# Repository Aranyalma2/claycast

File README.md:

**ClayCast** is a modular wireless control system for clay pigeon shooting ranges.  
It enables field centralized game management via a touchscreen **HMI device**, which controls up to 10 clay thrower machines through a wireless **Modbus RTU** network.  
Communication is handled by **controller node** that act as wireless relays to **client devices** attached to each clay thrower.

## 🎯 Features

- **Modular, multi-device architecture**: HMI (master), Controller (relay), and Client (thrower control)
- **Game management interface** via 7-inch touchscreen HMI
  - Enable/Disable machines (up to 10)
  - Pre-configure next game (max throw, double, triple)
  - Monitor clay disk levels with low-ammo alarms
  - Game screen
  - Summary screen
- **Wireless Modbus RTU bridging** over HC12 (~433MHz)
  - Up to **255 clients** per controller (practically limited to fewer)
  - Reliable full-frame encapsulation (no packet fragmentation)
- **Low-latency protocol** using UART and lightweight firmware
- Built with **Arduino framework**, **Atmega328p**, **ESP32**, and **HC12 modules**
- **Open and customizable** — easy to extend or adapt for other range configurations

## 🧩 Core Components

**ClayCast** consists of three main components:

### 💠 HMI Device
- Acts as the **Modbus RTU Master**
- Human-Machine Interface with touchscreen
- Controls up to **10 clay thrower machines**
- Manages and runs the **preconfigured game**
- Monitors **ammo levels** and triggers alarms if low
- Central command and monitoring unit for the entire system  
[More about here](hmi/README.md)

### 🔸 Controller
- Acts as a wireless Modbus RTU bridge
- Receives Modbus requests from a master device via UART (RS485)
- Encapsulates and broadcasts packets wirelessly to clients
- Receives wireless responses, decapsulates, and forwards them to the master  
[More about here](controller/README.md)

### 🔹 Client
- Identified by a unique Modbus slave address
- Controls an individual clay thrower machine
- Listens for Modbus requests, executes commands (e.g., fire), and returns status
- Response-only device; never initiates communication  
[More about here](client/README.md)

## 📡 Communication Flow

1. HMI sends Modbus RTU request to Controller via UART (RS485).
2. Controller encapsulates and transmits over HC12 radio.
3. Target Client receives, executes, and responds.
4. Controller decapsulates and returns response to HMI.

## 🛠️ Hardware Requirements

- **HMI Device**:
  - Kinco HMI [GL070E](https://en.kinco.cn/productdetail/gl070e90.html)

- **Controller**:
  - Arduino (Atmega328p)
  - HC12 radio module
  - RS485 interface to HMI (Modbus master)

- **Client**:
  - Arduino (Atmega328p)
  - HC12 radio module
  - Clay thrower trigger mechanism (relay, microswitch, etc.)

## 📦 Modbus Support

Clients implement:
- **Trigger register** – Fire the clay thrower
- **Status registers** – Report state, diagnostics, or ammo level

## 🚧 Status & Development Milestones

🛠️ Currently Under Development — Working Prototype Deployed in Test Field

- ✅ **Prototype Hardware Evaluation**  
  Initial testing and validation of temporary hardware components.

- ✅ **Firmware Architecture Design**  
  Core structure and logic for both controller and client firmware defined and implemented.

- ✅ **Interim Hardware Integration**  
  Temporary hardware assembled and tested for early firmware and communication debugging.

- ✅ **Wireless Communication Tester**  
  Radio signal testing module completed to assess transmission range and reliability.

- 🔧 **Final Hardware Assembly** *(In Progress)*  
  Development and deployment of production-ready, dedicated hardware.
  
- 🚀 **Human-Machine Interface (HMI)** *(In Testing)*  
  - Game customizability, fire control, data logging  
  - Ammo monitoring with alarms  
  - Controls up to 10 clay throwers

## 🔀 Alternative use

Create a Modbus RTU bridge over the air with 2 or more **Controllers**. However, radio medium usage is not controlled, so it is easy to cause interference. Incidentally it does not include any error detection and/or correction, leaving everything to the application layer protocol.
Not ready for any production usage.

---

## 📜 License

This project is licensed under the MIT License. See the [LICENSE](LICENSE.md) file for details.

---

## 🤝 Contributions

Made with ❤️ by <a href="https://github.com/Aranyalma2" target="_blank">Aranyalma2</a>

This is a self-maintained project. Feel free to use, fork, or modify it. Feedback and suggestions are always welcome!

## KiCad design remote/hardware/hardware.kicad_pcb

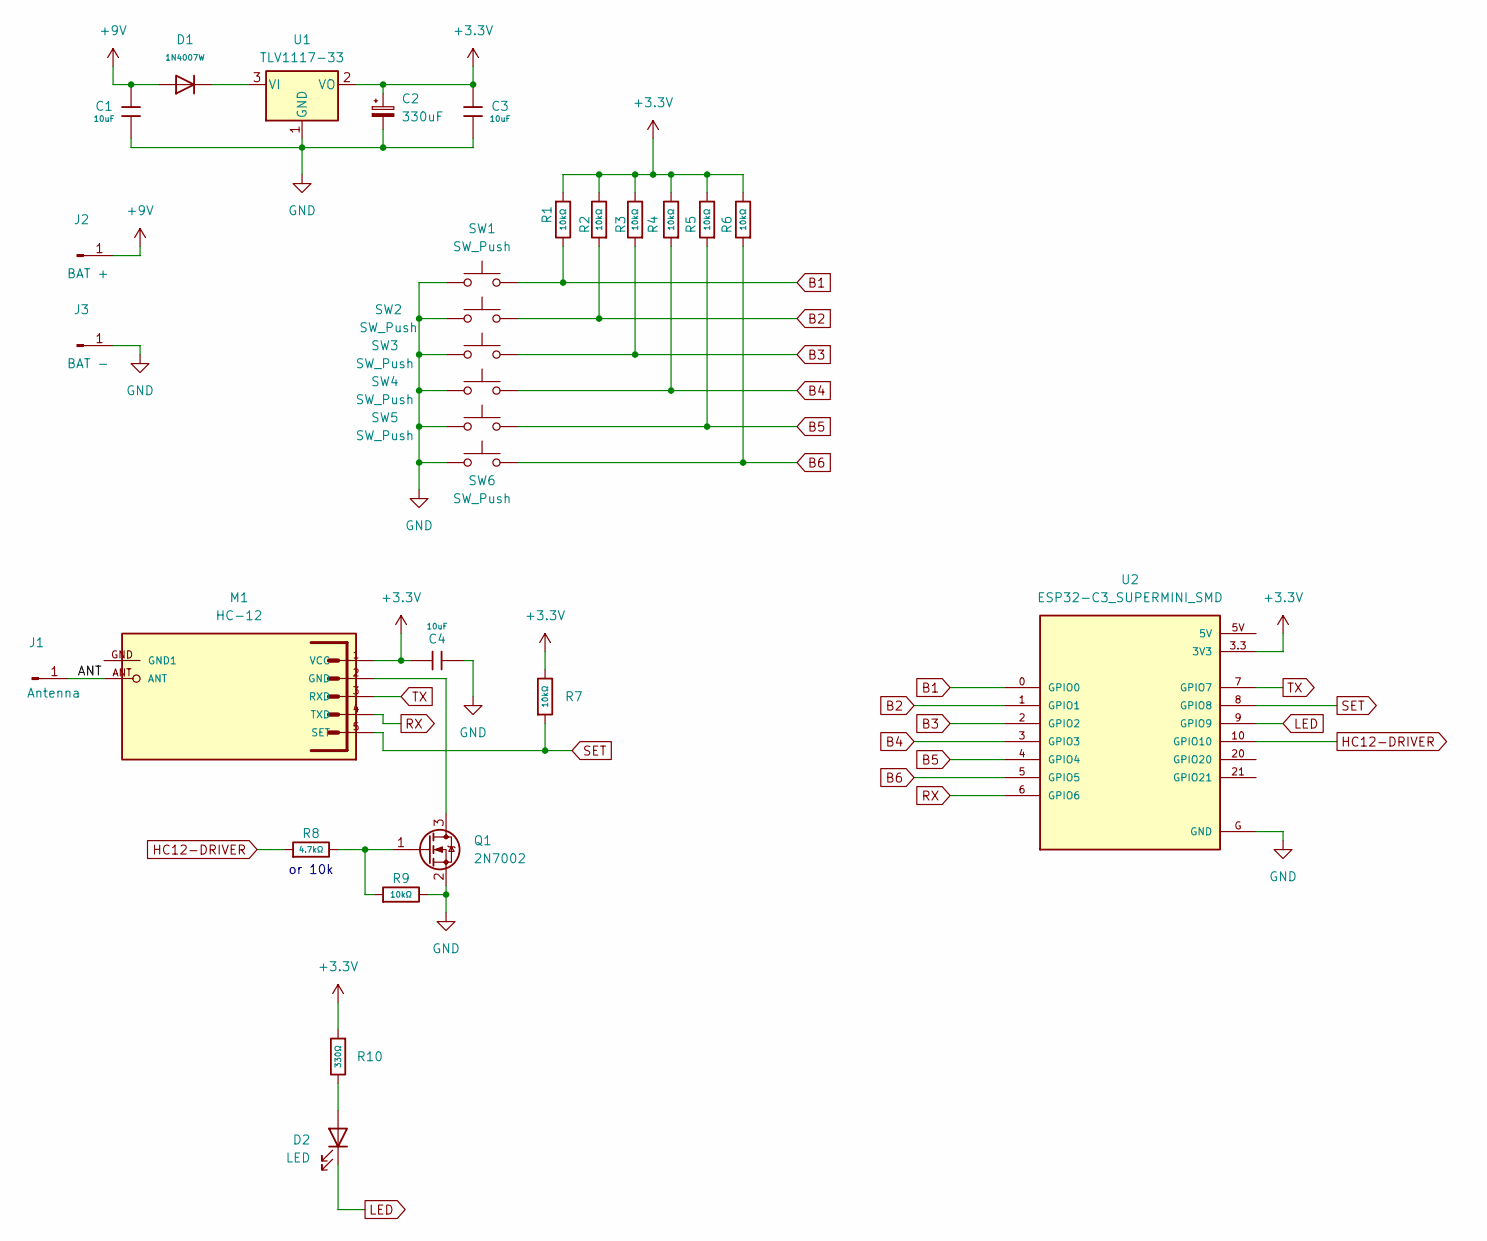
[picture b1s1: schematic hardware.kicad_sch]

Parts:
C1, C3, C4: 10uF; C_1206; Voltage Rated 6V; Tolerance ±10%; Part CL31A106KBHNNNE; LCSC C13585
C2: 330uF; CP_Radial_D6.3mm_P2.50mm
D1: 1N4007W; D_SMB; Part 1N4007W; LCSC C18199088
D2: LED; LED_1206_3216Metric_Pad1.42x1.75mm_HandSolder
J1: Antenna; PinHeader_1x01_P1.00mm_Vertical
J2: BAT +; PinHeader_1x01_P1.00mm_Vertical
J3: BAT -; PinHeader_1x01_P1.00mm_Vertical
M1: HC-12; MA05-1
Q1: 2N7002; SOT-23
R1, R2, R3, R4, R5, R6, R7, R9: 10kΩ; R_0805; Overload Voltage (Max) 200V; Tolerance ±1%; Part 1206W4F1002T5E; LCSC C17902
R8: 4.7kΩ; R_0805; Overload Voltage (Max) 200V; Tolerance ±1%; Part 1206W4F1002T5E; LCSC C17902
R10: 330Ω; R_1206
SW1, SW2, SW3, SW4, SW5, SW6: SW_Push; SW_Push_1P1T_NO_E-Switch_TL3301NxxxxxG
U1: TLV1117-33; TO-252-2
U2: ESP32-C3_SUPERMINI_SMD; MODULE_ESP32-C3_SUPERMINI

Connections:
+3.3V: C2.1, C3.1, C4.1, M1.1 (VCC), R1.1, R2.2, R3.2, R4.2, R5.2, R6.2, R7.2, R10.1, U1.2 (VO), U2.3.3 (3V3)
+9V: C1.1, D1.2, J2.1
/ANT: J1.1, M1.ANT
B1: R1.2, SW1.1, U2.0 (GPIO0)
B2: R2.1, SW2.1, U2.1 (GPIO1)
B3: R3.1, SW3.1, U2.2 (GPIO2)
B4: R4.1, SW4.1, U2.3 (GPIO3)
B5: R5.1, SW5.1, U2.4 (GPIO4)
B6: R6.1, SW6.1, U2.5 (GPIO5)
GND: C1.2, C2.2, C3.2, C4.2, J3.1, Q1.2 (S), R9.2, SW1.2, SW2.2, SW3.2, SW4.2, SW5.2, SW6.2, U1.1 (GND), U2.G (GND)
HC12-DRIVER: R8.1, U2.10 (GPIO10)
LED: D2.1 (K), U2.9 (GPIO9)
unnamed: D2.2 (A), R10.2
unnamed: M1.2 (GND), Q1.3 (D)
unnamed: Q1.1 (G), R8.2, R9.1
unnamed: D1.1, U1.3 (VI)
RX: M1.4 (TXD), U2.6 (GPIO6)
SET: M1.5 (SET), R7.1, U2.8 (GPIO8)
TX: M1.3 (RXD), U2.7 (GPIO7)

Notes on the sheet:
or 10k

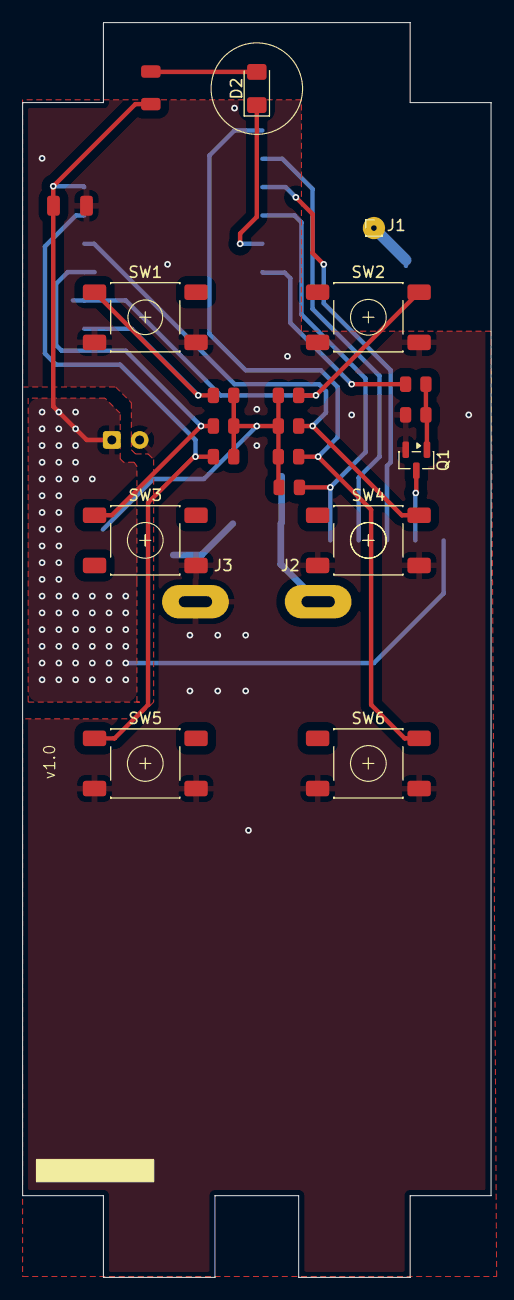
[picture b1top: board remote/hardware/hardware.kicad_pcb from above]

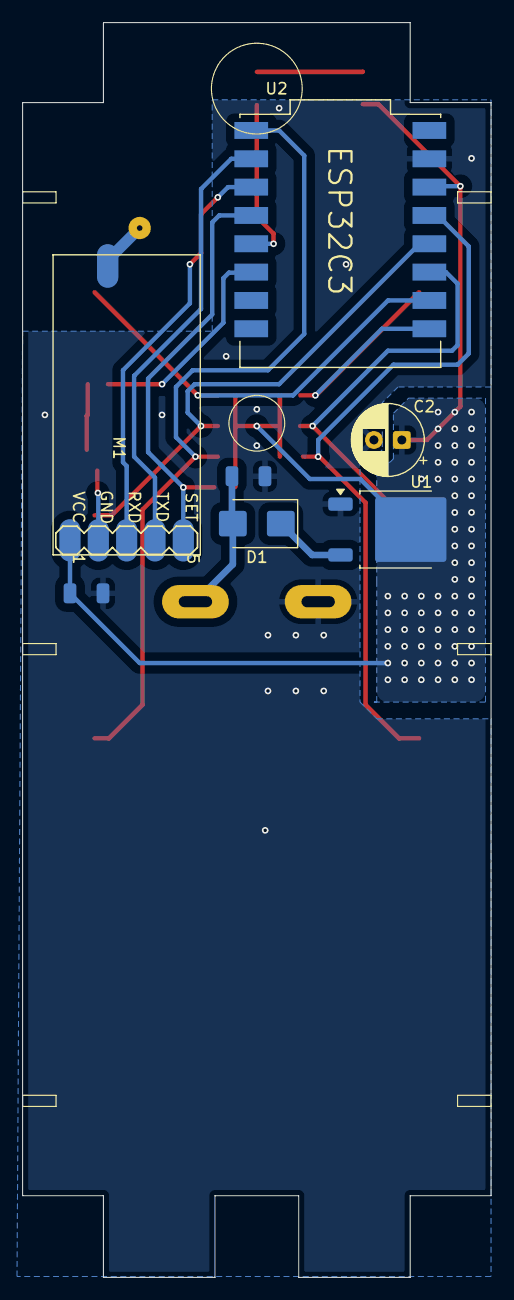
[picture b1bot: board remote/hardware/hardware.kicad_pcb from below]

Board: 2 copper layers, 42.0 x 112.5 mm, 29 parts (7 on the bottom side), 19 nets.

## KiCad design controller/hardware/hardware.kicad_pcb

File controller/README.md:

## The core tasks of the controller

### 📡 Serial Communication Setup

- Uses **hardware `Serial`** for UART communication with the Modbus RTU master
- Uses **`SoftwareSerial`** or a secondary UART for the HC12 module

### 📦 Modbus RTU Data Encapsulation

- Reads Modbus RTU requests from UART
- Wraps requests in a custom protocol header for wireless transmission via HC12

### 🚀 HC12 Transmission

- Sends encapsulated Modbus RTU requests over HC12
- Receives wrapped responses wirelessly from the client

### 📥 Response Processing

- Validates incoming wrapped responses
- Unwraps the Modbus RTU data
- Forwards it back to the Modbus master via hardware `Serial`

### 🧪 Test Mode (Enabled via A0)

If **pin A0 is HIGH** during power-up or reset, the controller enters **testing mode**:

- It disables Modbus forwarding
- Instead, it periodically sends test messages over HC12 in the following format:

`Testing in progress: {n}`

- These messages are wrapped in the standard packet format below and sent every ~500ms
- `n` is an incrementing counter used to test communication reliability and packet loss

This mode is useful for verifying wireless reception, packet framing, and performance of the client-side system.

---

## 📦 Data Encapsulation Format

All HC12-transmitted messages use a consistent wrapper protocol:

```
+--------------------+---------+----------------------+
| Field              | Size    | Description          |
+--------------------+---------+----------------------+
| Start byte (0xAA)  | 1 Byte  | Packet start byte    |
| Data size          | 2 Bytes | Data size            |
| Data               | X Bytes | Modbus RTU package   |
| Checksum           | 2 Bytes | Size + Data checksum |
| End byte (0x55)    | 1 Byte  | Packet end byte      |
+--------------------+---------+----------------------+
```

- The `Data` section contains a complete Modbus RTU request or response
- Destination is determined by the Modbus RTU address field inside the data

## 🔧 Notes

- Make sure the HC12 modules are on the same channel (e.g. `CH050`)
- The serial and HC12 baudrates may differ, but it is recommended to choose equal and low rates. However, it is important to match the timing of the packet frames.

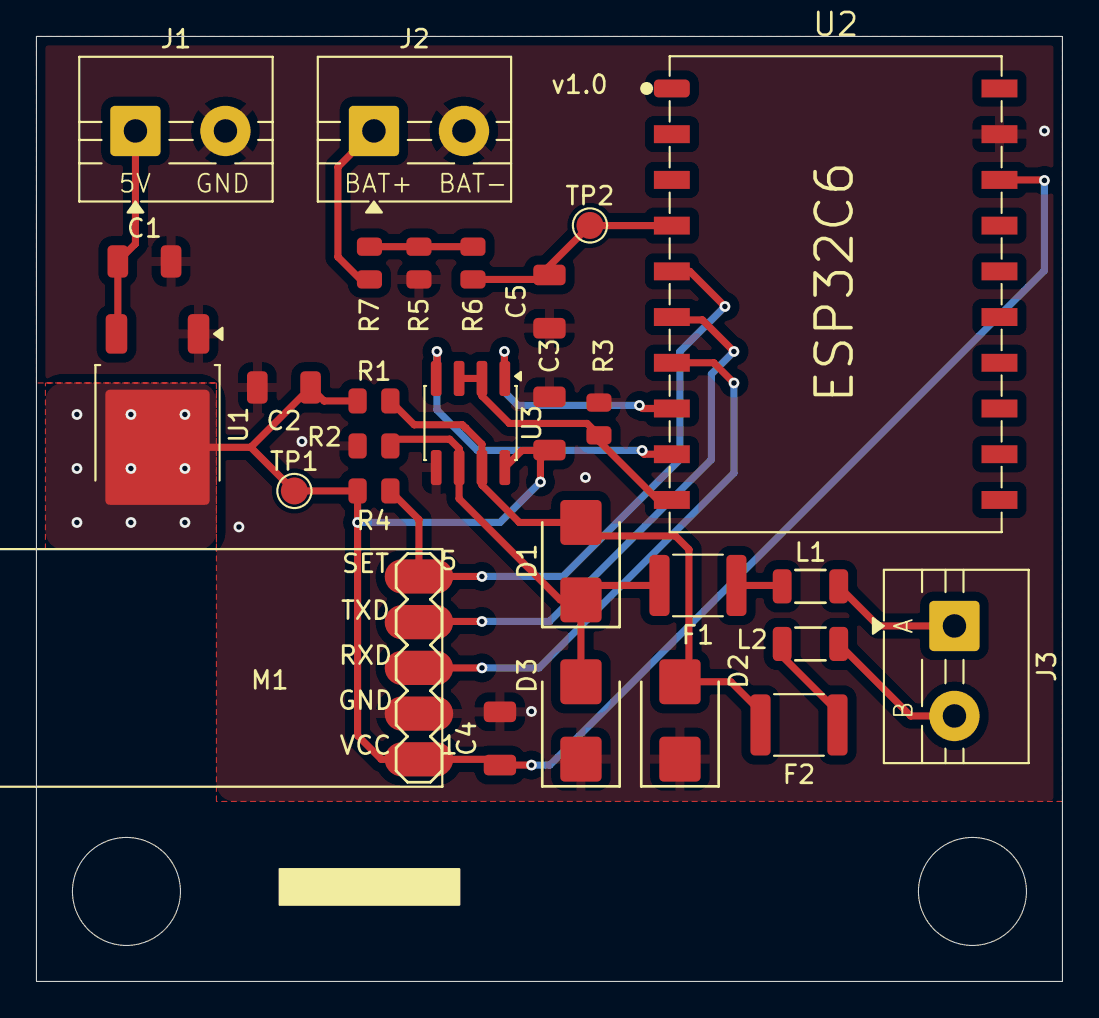
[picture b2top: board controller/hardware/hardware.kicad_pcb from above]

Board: 2 copper layers, 57.0 x 52.5 mm, 28 parts (0 on the bottom side), 18 nets.

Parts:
C1, C2, C4: 10uF; C_1206
C3, C5: 100nF; C_1206
D1, D2, D3: SMBJ12CA; D_SMB
F1, F2: BSMD1812-100-30V
J1, J2, J3: Screw_Terminal_01x02; TerminalBlock_MaiXu_MX126-5.0-02P_1x02_P5.00mm
L1, L2: 10uH; L_1206
M1: HC-12; MA05-1
R1, R2, R3, R4: 10kΩ; R_0805
R5: 1MΩ; R_0805
R6: 1kΩ; R_0805
R7: 100kΩ; R_0805
TP1: 3V3; TestPoint_Pad_D1.5mm
TP2: BAT_V; TestPoint_Pad_D1.5mm
U1: TLV1117-33; TO-252-2
U2: ESP32-C6-SuperMini; ESP32-C6-SuperMini_SMD
U3: MAX3485; SOIC-8_3.9x4.9mm_P1.27mm

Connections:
+3.3V: C2.1, C3.1, C4.1, M1.1 (VCC), R1.1, R4.2, TP1.1, U1.2 (VO), U2.13 (3V3), U3.8 (VCC)
+5V: C1.1, J1.1, U1.3 (VI)
+BATT: J2.1, R5.2
BAT_MEASURE: C5.2, R6.1, TP2.1, U2.4 (GPIO1)
GND: C1.2, C2.2, C3.2, C4.2, C5.1, D2.1, D3.1, J1.2, J2.2, M1.2 (GND), R2.2, R3.2, R7.1, U1.1 (GND), U2.12 (GND), U3.5 (GND)
unnamed: F1.2, L1.1
unnamed: F2.2, L2.1
unnamed: R5.1, R6.2, R7.2
unnamed: D1.1, D3.2, F1.1, R2.1, U3.6 (A)
unnamed: D1.2, D2.2, F2.1, R1.2, U3.7 (B)
RS485-1_A: J3.1, L1.2
RS485-1_B: J3.2, L2.2
RX: M1.4 (TXD), U2.6 (GPIO3)
RX1: U2.8 (GPIO5), U3.1 (RO)
SET: M1.5 (SET), R4.1, U2.5 (GPIO2)
TX: M1.3 (RXD), U2.7 (GPIO4)
TX1: U2.9 (GPIO6), U3.4 (DI)
TX1_EN: R3.1, U2.10 (GPIO7), U3.2 (~RE), U3.3 (DE)

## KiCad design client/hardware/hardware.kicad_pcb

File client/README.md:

## The Core Tasks of the Client

### 📡 Setup Serial Communication

- Uses `SoftwareSerial` for UART communication with the HC12 wireless module  
- Uses hardware `Serial` for debug output

### 📥 Process Modbus RTU Requests

- Waits for incoming encapsulated Modbus RTU requests over HC12  
- Unwraps received packets and validates structure and checksum

### ⚙️ Handle Modbus Logic

- Supports:
  - Read Holding Registers (`0x03`)
  - Write Single Register (`0x06`)
- Maintains internal holding registers for:
  - Device ID
  - Shoot trigger
  - Success flag (Complex/Simple)
- Triggers actions based on incoming Modbus commands

#### 🧮 Registers

**Holding Register (4xxxxx)**
```
+---------+----------------------------+
| Address | Description                |
+---------+----------------------------+
| 0x00    | Modbus Address (Read only) |
| 0x01    | Fire (automatic zeroing)   |
| 0x02    | IN1 (zeroing at fire)      |
| 0x03    | IN2 (Raw)                  |
+---------+----------------------------+
```

### 📤 Transmit Modbus RTU Responses

- Wraps Modbus RTU responses with a protocol header  
- Sends the encapsulated data back via HC12

---

## 📦 Data Encapsulation Format

All HC12-transmitted messages use a consistent wrapper protocol:

```
+--------------------+---------+----------------------+
| Field              | Size    | Description          |
+--------------------+---------+----------------------+
| Start byte (0xAA)  | 1 Byte  | Packet start byte    |
| Data size          | 2 Bytes | Data size            |
| Data               | X Bytes | Modbus RTU package   |
| Checksum           | 2 Bytes | Size + Data checksum |
| End byte (0x55)    | 1 Byte  | Packet end byte      |
+--------------------+---------+----------------------+
```

- The `Data` section contains a complete Modbus RTU request or response
- Destination is determined by the Modbus RTU address field inside the data

---

## 🔧 Notes

- Make sure the HC12 modules are on the same channel (e.g. `CH050`)  
- The client listens for shoot commands and activates GPIO pins accordingly

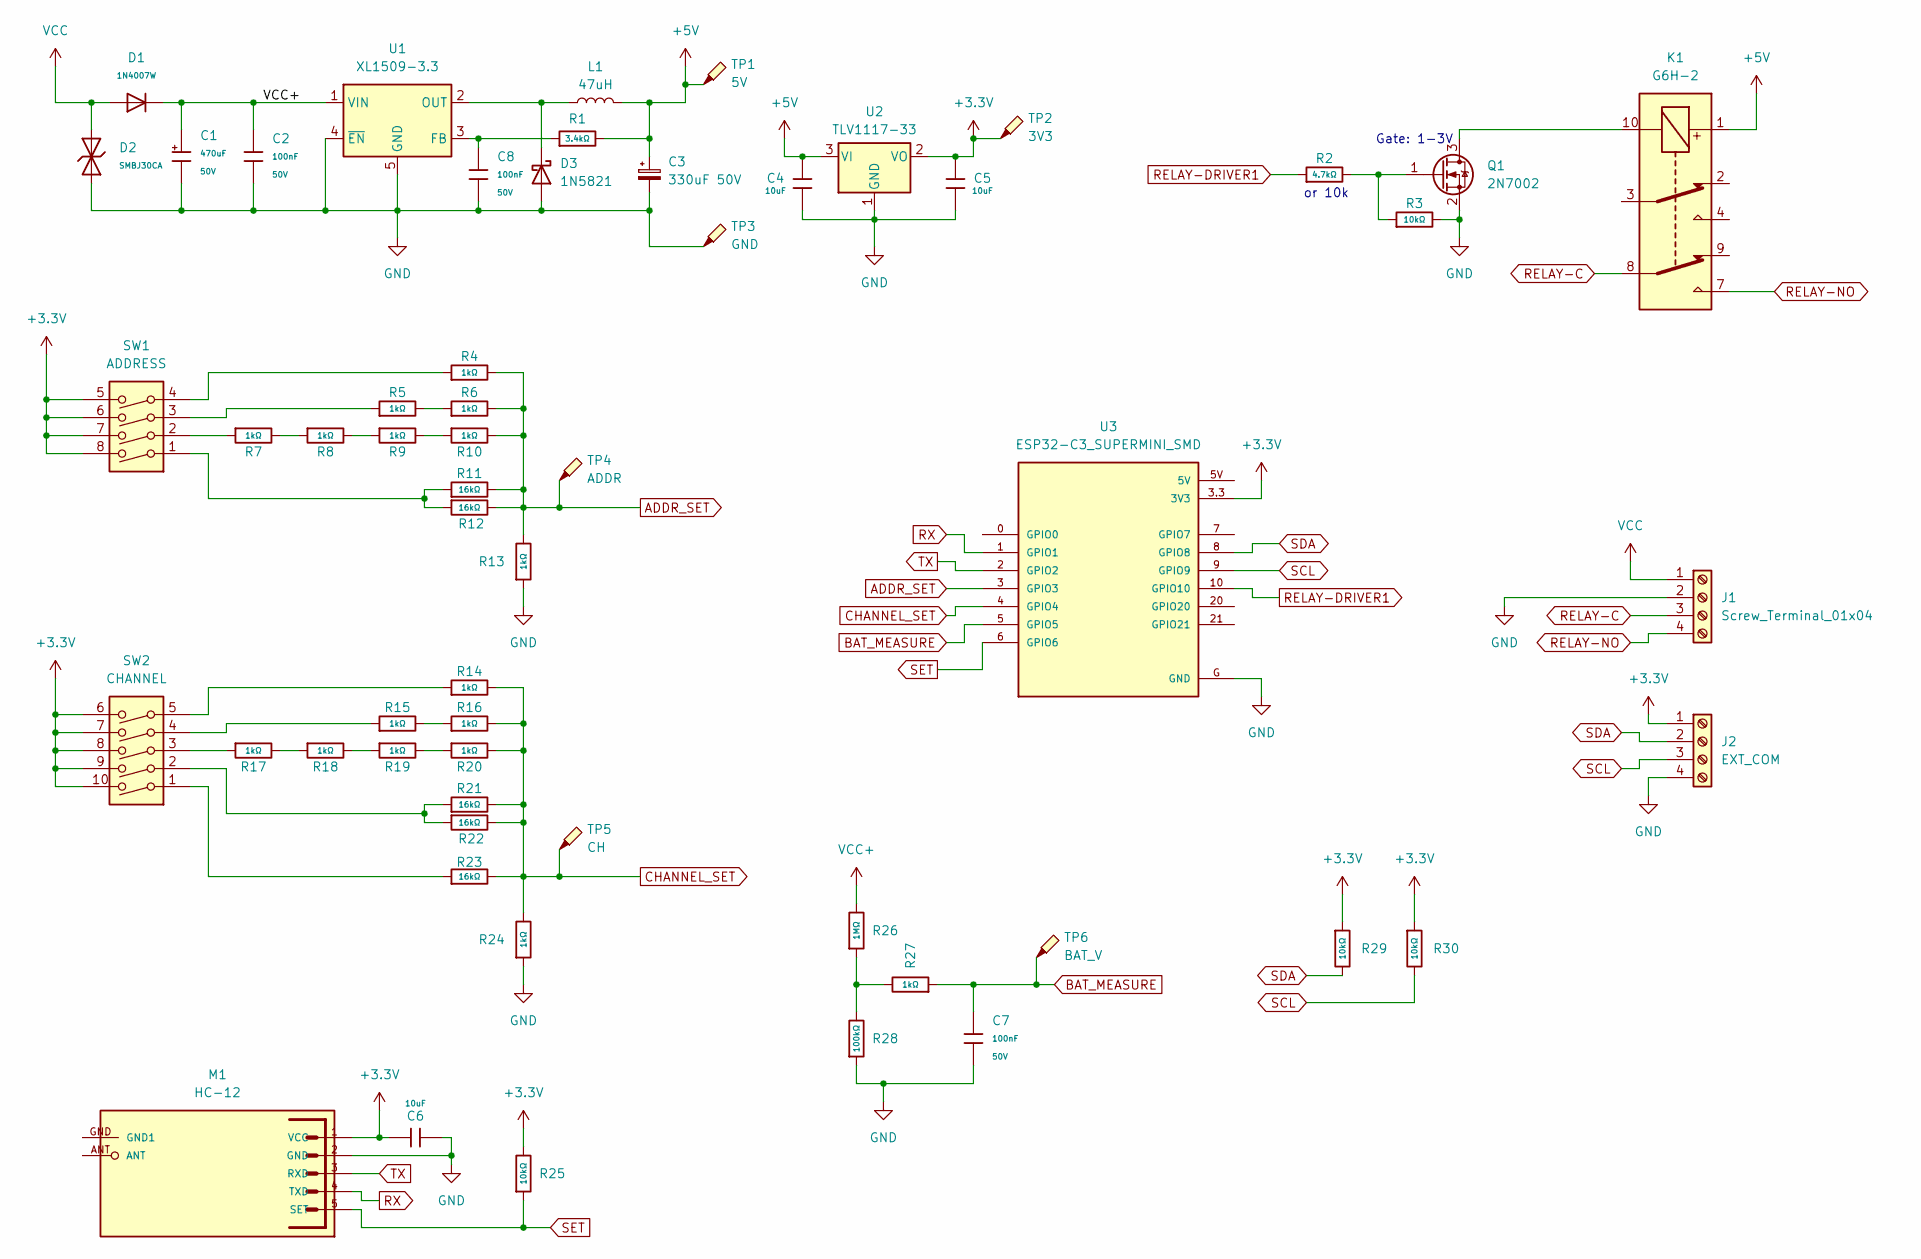
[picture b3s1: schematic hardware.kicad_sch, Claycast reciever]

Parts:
C1: 470uF; C_Plugin,D10xL16mm; Voltage Rated 50V; Part EGT477M1HG16RRS0P; LCSC C3015599
C2, C7, C8: 100nF; C_1206; Voltage Rated 50V; Tolerance ±10%; Part CL31B104KBCNNNC; LCSC C24497
C3: 330uF 50V; CP_Radial_D6.3mm_P2.50mm
C4, C5, C6: 10uF; C_1206; Voltage Rated 6V; Tolerance ±10%; Part CL31A106KBHNNNE; LCSC C13585
D1: 1N4007W; D_SMB; Part 1N4007W; LCSC C18199088
D2: SMBJ30CA; D_SMB; Breakdown Voltage 33.3V; Part SMBJ30CA; LCSC C2925441
D3: 1N5821; D_SMB
J1: Screw_Terminal_01x04; General Connector 4P 3.5mm - Socket
J2: EXT_COM; JST_PH_B4B-PH-K_1x04_P2.00mm_Vertical
K1: G6H-2; Relay_DPDT_Omron_G6H-2
L1: 47uH; L_Radial_D7.0mm_P3.00mm
M1: HC-12; MA05-1
Q1: 2N7002; SOT-23
R1: 3.4kΩ; R_0805; Overload Voltage (Max) 150V; Tolerance ±1%; Part 0805W8F3303T5E; LCSC C17629
R2: 4.7kΩ; R_0805; Overload Voltage (Max) 200V; Tolerance ±1%; Part 1206W4F1002T5E; LCSC C17902
R3, R25, R29, R30: 10kΩ; R_0805; Overload Voltage (Max) 200V; Tolerance ±1%; Part 1206W4F1002T5E; LCSC C17902
R4, R5, R6, R7, R8, R9, R10, R13, R14, R15, R16, R17, R18, R19, R20, R24, R27: 1kΩ; R_0805; Overload Voltage (Max) 200V; Tolerance ±1%; Part 1206W4F1002T5E; LCSC C17902
R11, R12, R21, R22, R23: 16kΩ; R_0805; Overload Voltage (Max) 200V; Tolerance ±1%; Part 1206W4F1002T5E; LCSC C17902
R26: 1MΩ; R_0805; Overload Voltage (Max) 200V; Tolerance ±1%; Part 1206W4F1002T5E; LCSC C17902
R28: 100kΩ; R_0805; Overload Voltage (Max) 200V; Tolerance ±1%; Part 1206W4F1002T5E; LCSC C17902
SW1: ADDRESS; SW_DIP_SPSTx04_Slide_9.78x12.34mm_W7.62mm_P2.54mm
SW2: CHANNEL; SW_DIP_SPSTx05_Slide_9.78x14.88mm_W7.62mm_P2.54mm
TP1: 5V; TestPoint_Pad_D1.5mm
TP2: 3V3; TestPoint_Pad_D1.5mm
TP3: GND; TestPoint_Pad_D1.5mm
TP4: ADDR; TestPoint_Pad_D1.5mm
TP5: CH; TestPoint_Pad_D1.5mm
TP6: BAT_V; TestPoint_Pad_D1.5mm
U1: XL1509-3.3; SOIC-8_3.9x4.9mm_P1.27mm
U2: TLV1117-33; TO-252-2
U3: ESP32-C3_SUPERMINI_SMD; MODULE_ESP32-C3_SUPERMINI

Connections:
+3.3V: C5.1, C6.1, J2.1, M1.1 (VCC), R25.2, R29.1, R30.1, SW1.5, SW1.6, SW1.7, SW1.8, SW2.6, SW2.7, SW2.8, SW2.9, SW2.10, TP2.1, U2.2 (VO), U3.3.3 (3V3)
+5V: C3.1, C4.1, K1.1, L1.2, R1.2, TP1.1, U2.3 (VI)
ADDR_SET: R4.2, R6.2, R10.2, R11.2, R12.2, R13.2, TP4.1, U3.3 (GPIO3)
BAT_MEASURE: C7.2, R27.1, TP6.1, U3.5 (GPIO5)
CHANNEL_SET: R14.2, R16.2, R20.2, R21.2, R22.2, R23.2, R24.2, TP5.1, U3.4 (GPIO4)
GND: C1.2, C2.2, C3.2, C4.2, C5.2, C6.2, C7.1, C8.2, D2.1, D3.2 (A), J1.2, J2.4, M1.2 (GND), Q1.2 (S), R3.2, R13.1, R24.1, R28.1, TP3.1, U1.4 (~EN), U1.5 (GND), U1.6 (GND), U1.7 (GND), U1.8 (GND), U2.1 (GND), U3.G (GND)
unnamed: D3.1 (K), L1.1, U1.2 (OUT)
unnamed: K1.10, Q1.3 (D)
unnamed: Q1.1 (G), R2.2, R3.1
unnamed: R4.1, SW1.4
unnamed: R5.1, SW1.3
unnamed: R5.2, R6.1
unnamed: R7.1, SW1.2
unnamed: R7.2, R8.1
unnamed: R8.2, R9.1
unnamed: R9.2, R10.1
unnamed: R11.1, R12.1, SW1.1
unnamed: R14.1, SW2.5
unnamed: R15.1, SW2.4
unnamed: R15.2, R16.1
unnamed: R17.1, SW2.3
unnamed: R17.2, R18.1
unnamed: R18.2, R19.1
unnamed: R19.2, R20.1
unnamed: R21.1, R22.1, SW2.2
unnamed: R23.1, SW2.1
unnamed: R26.1, R27.2, R28.2
unnamed: C8.1, R1.1, U1.3 (FB)
RELAY-C: J1.3, K1.8
RELAY-DRIVER1: R2.1, U3.10 (GPIO10)
RELAY-NO: J1.4, K1.7
RX: M1.4 (TXD), U3.1 (GPIO1)
SCL: J2.3, R30.2, U3.9 (GPIO9)
SDA: J2.2, R29.2, U3.8 (GPIO8)
SET: M1.5 (SET), R25.1, U3.6 (GPIO6)
TX: M1.3 (RXD), U3.2 (GPIO2)
VCC: D1.2, D2.2, J1.1
VCC+: C1.1, C2.1, D1.1, R26.2, U1.1 (VIN)

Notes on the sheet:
or 10k
Gate: 1-3V

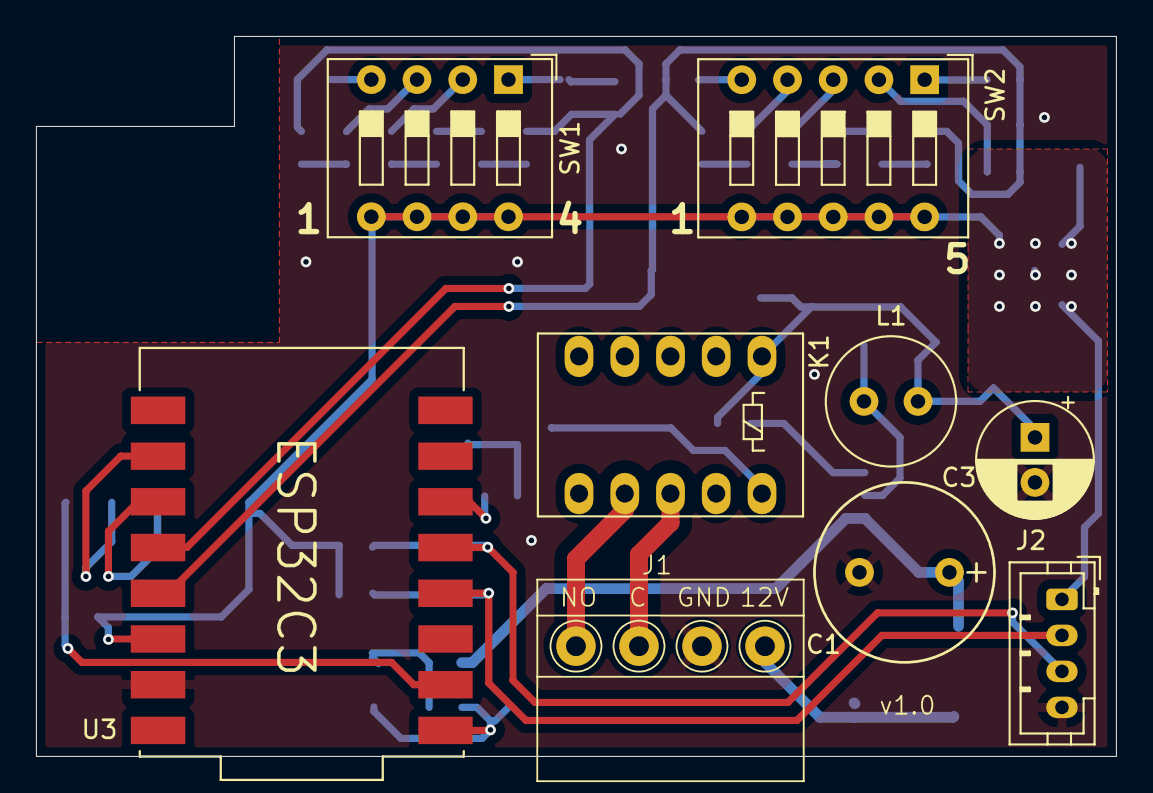
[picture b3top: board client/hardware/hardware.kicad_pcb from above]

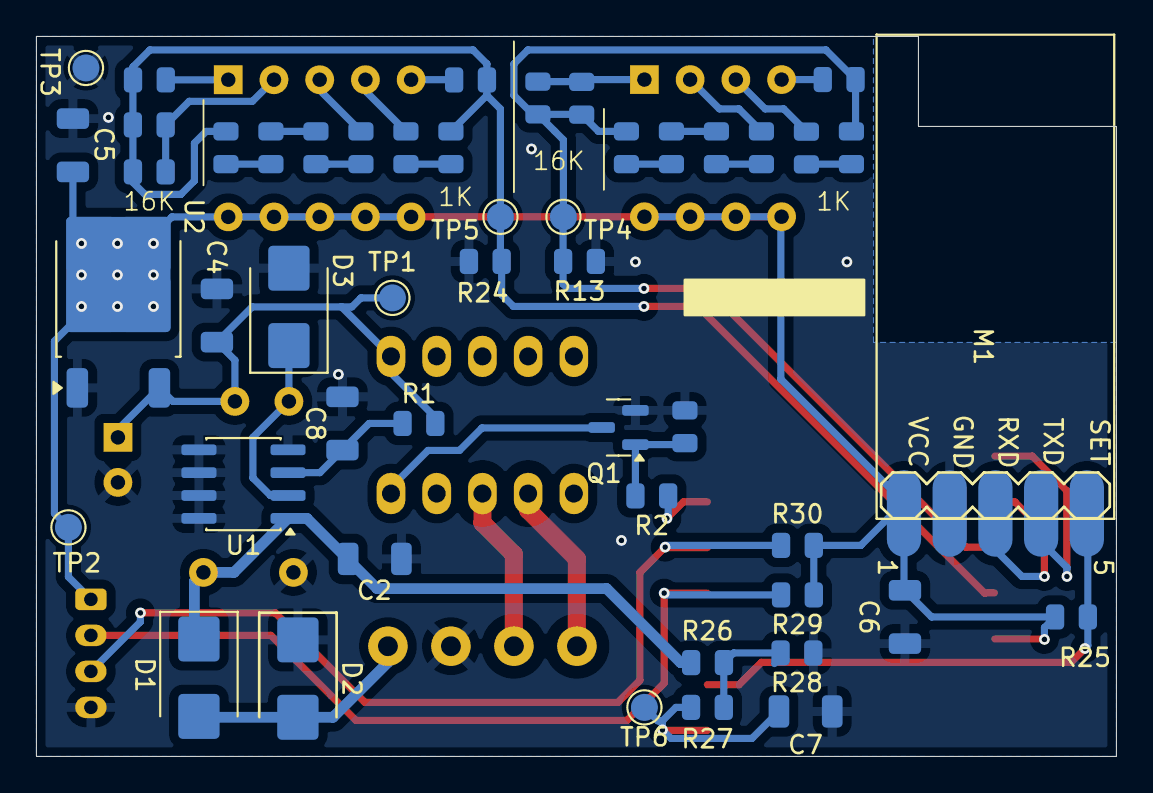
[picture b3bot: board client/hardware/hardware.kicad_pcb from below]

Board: 2 copper layers, 60.0 x 40.0 mm, 58 parts (49 on the bottom side), 38 nets.

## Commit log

2025-04-10 init
    * readme with simple spec
    * logo and banner
2025-04-10 controller & client
2025-04-18 test files
2025-04-22 delay hc12 serial read
2025-04-22 update some readmes
2025-04-22 v1.0
    # Pre-release of v1.0
    ## Controller
    * Remove time sensitive and blocking parts
    * Monogamous defines and parameters
    * Remove DEBUG from compile
    * Optimes buffer usage
2025-04-29 v1.0.1 - tweaks
    * Add testing mode for controller
    * Create a dedicated receiving tester
    * Tweaks for hardware
2025-04-30 Kinco HMI
    Human machine interface and game controller
    Up to 10 machine
    Support Hungarian language only
    *Use [Kinco DTools V4.5.0.1](https://en.kinco.cn/download/hmisoftware.html)*
2025-04-30 Update README.md
    Add info about HMI and update core components list with it.
2025-05-01 fix machine 5 data transfer
2025-05-08 Release v1.1.0
    Add client fire timout (fix multi fire by lost modbus response )
    Add scan window (only test fire available yet)
2025-05-15 add build scripts
    + set lower fire timeout
2025-05-16 set lower delay
    set minimum delay to 4 sec
2026-05-27 remove the v1 files
2026-06-05 receiver pcb v1
2026-06-05 controller init
2026-06-05 client fw v1
2026-06-05 update to kicad v9
2026-06-05 hw updates
2026-06-06 remote init
2026-06-11 final v1.0 hardware
